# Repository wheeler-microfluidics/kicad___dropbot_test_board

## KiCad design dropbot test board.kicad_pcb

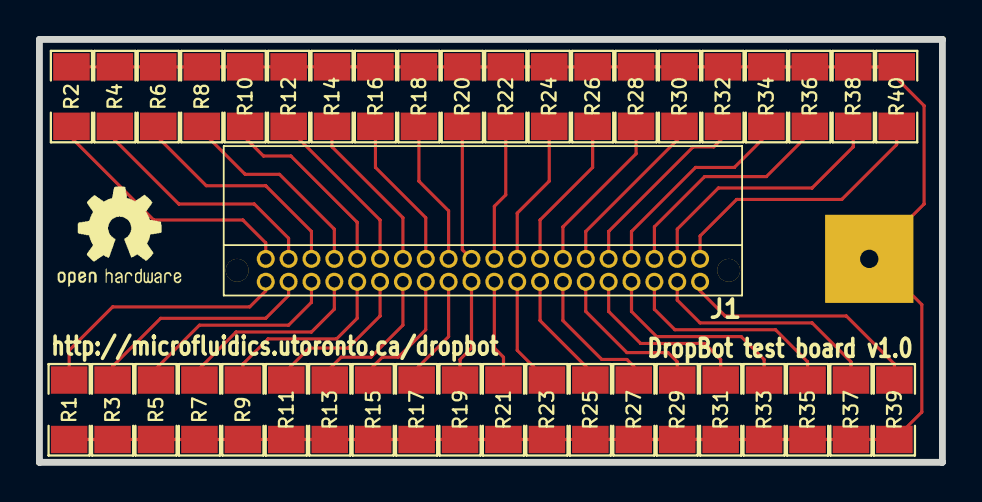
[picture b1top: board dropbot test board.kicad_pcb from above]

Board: 2 copper layers, 50.2 x 23.5 mm, 42 parts (0 on the bottom side), 41 nets.

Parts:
J1: CONN_40; TFML-120-01-XXX-D-RA
P1: CONN_1; 4.9mm_DMF_Electrode
R1, R2, R3, R4, R5, R6, R7, R8, R9, R10, R11, R12, R13, R14, R15, R16, R17, R18, R19, R20, R21, R22, R23, R24, R25, R26, R27, R28, R29, R30, R31, R32, R33, R34, R35, R36, R37, R38, R39, R40: R; SM1206

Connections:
unnamed: J1.1, R1.1
unnamed: J1.36, R36.1
unnamed: J1.33, R33.1
unnamed: J1.14, R14.1
unnamed: J1.24, R24.1
unnamed: J1.34, R34.1
unnamed: J1.15, R15.1
unnamed: J1.25, R25.1
unnamed: J1.35, R35.1
unnamed: J1.16, R16.1
unnamed: J1.26, R26.1
unnamed: J1.23, R23.1
unnamed: J1.17, R17.1
unnamed: J1.27, R27.1
unnamed: J1.37, R37.1
unnamed: J1.18, R18.1
unnamed: J1.28, R28.1
unnamed: J1.38, R38.1
unnamed: J1.19, R19.1
unnamed: J1.29, R29.1
unnamed: J1.39, R39.1
unnamed: J1.20, R20.1
unnamed: J1.2, R2.1
unnamed: J1.3, R3.1
unnamed: J1.4, R4.1
unnamed: J1.5, R5.1
unnamed: J1.6, R6.1
unnamed: J1.7, R7.1
unnamed: J1.8, R8.1
unnamed: J1.9, R9.1
unnamed: J1.10, R10.1
unnamed: J1.30, R30.1
unnamed: J1.40, R40.1
unnamed: J1.11, R11.1
unnamed: J1.21, R21.1
unnamed: J1.31, R31.1
unnamed: J1.12, R12.1
unnamed: J1.22, R22.1
unnamed: J1.32, R32.1
unnamed: J1.13, R13.1
unnamed: P1.1, R1.2, R2.2, R3.2, R4.2, R5.2, R6.2, R7.2, R8.2, R9.2, R10.2, R11.2, R12.2, R13.2, R14.2, R15.2, R16.2, R17.2, R18.2, R19.2, R20.2, R21.2, R22.2, R23.2, R24.2, R25.2, R26.2, R27.2, R28.2, R29.2, R30.2, R31.2, R32.2, R33.2, R34.2, R35.2, R36.2, R37.2, R38.2, R39.2, R40.2

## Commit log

2014-05-06 Resize pages to 8.5x11" and set metadata
2014-07-24 Convert BOM to csv
2014-08-05 Update pos files
2015-01-21 Update BOM
2015-08-26 Use vertical instead of right angle Samtec header
2016-01-20 Update .gitmodules file to point to github
2017-07-13 added appveyor.yml
2017-07-14 AppVeyor Configuration Updated
2017-07-15 AppVeyor Update: "5f61b891681557a9814440e47f9102b18ddcac59"
2017-07-17 AppVeyor Update: "ebd3acae5fa1c3216efbc6cb908b5db07f7b5100"
2017-07-17 AppVeyor Update: "f9cc8f1957b59965408d0c40c51fe03863cbf7a2"
2017-07-17 AppVeyor Update: "5d17439f61475bc23d95e0b42b680d8fb34545a9"
2017-07-18 AppVeyor Update: "ed2efe62bb2ab97aa8e77d59d2fbf27f7906765d"
2017-07-18 AppVeyor Update: "a4e909ac7a44d2708564d46a9b978b95c8367686"
2017-07-19 AppVeyor Update: "d5d159050eac48ab9123f383fe8e949476d7f60f"
2017-07-20 AppVeyor Update: "35852f667457a927c170bb71278740b12d7a8f75"
